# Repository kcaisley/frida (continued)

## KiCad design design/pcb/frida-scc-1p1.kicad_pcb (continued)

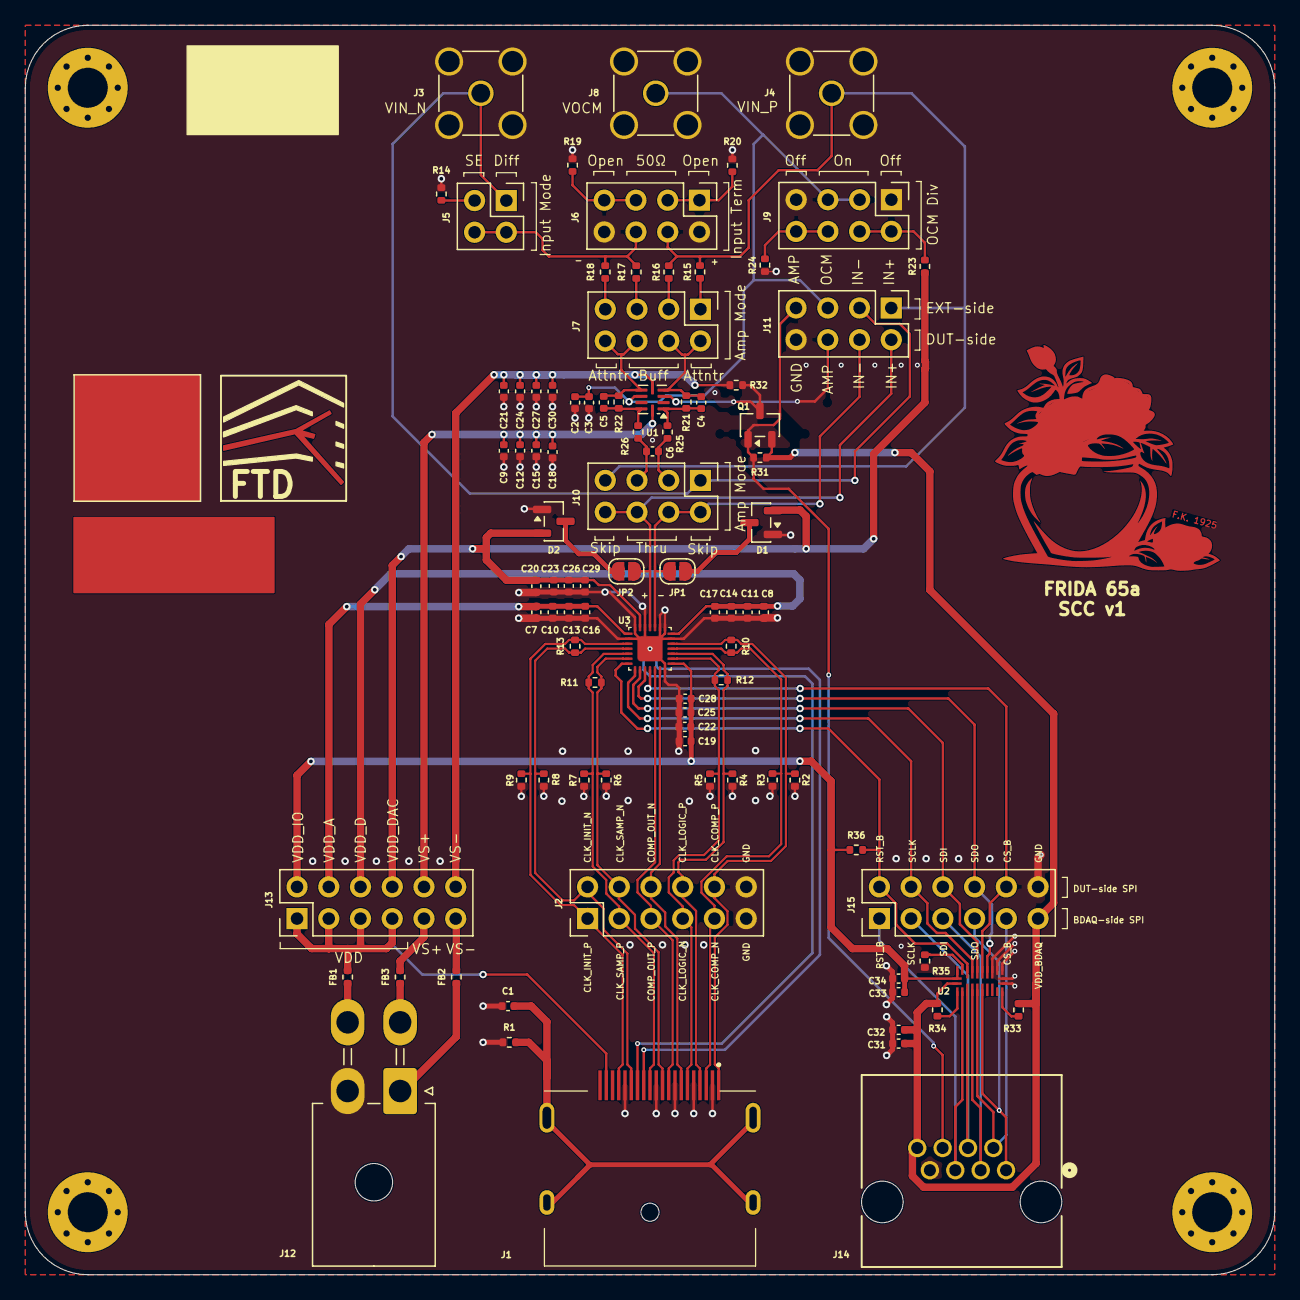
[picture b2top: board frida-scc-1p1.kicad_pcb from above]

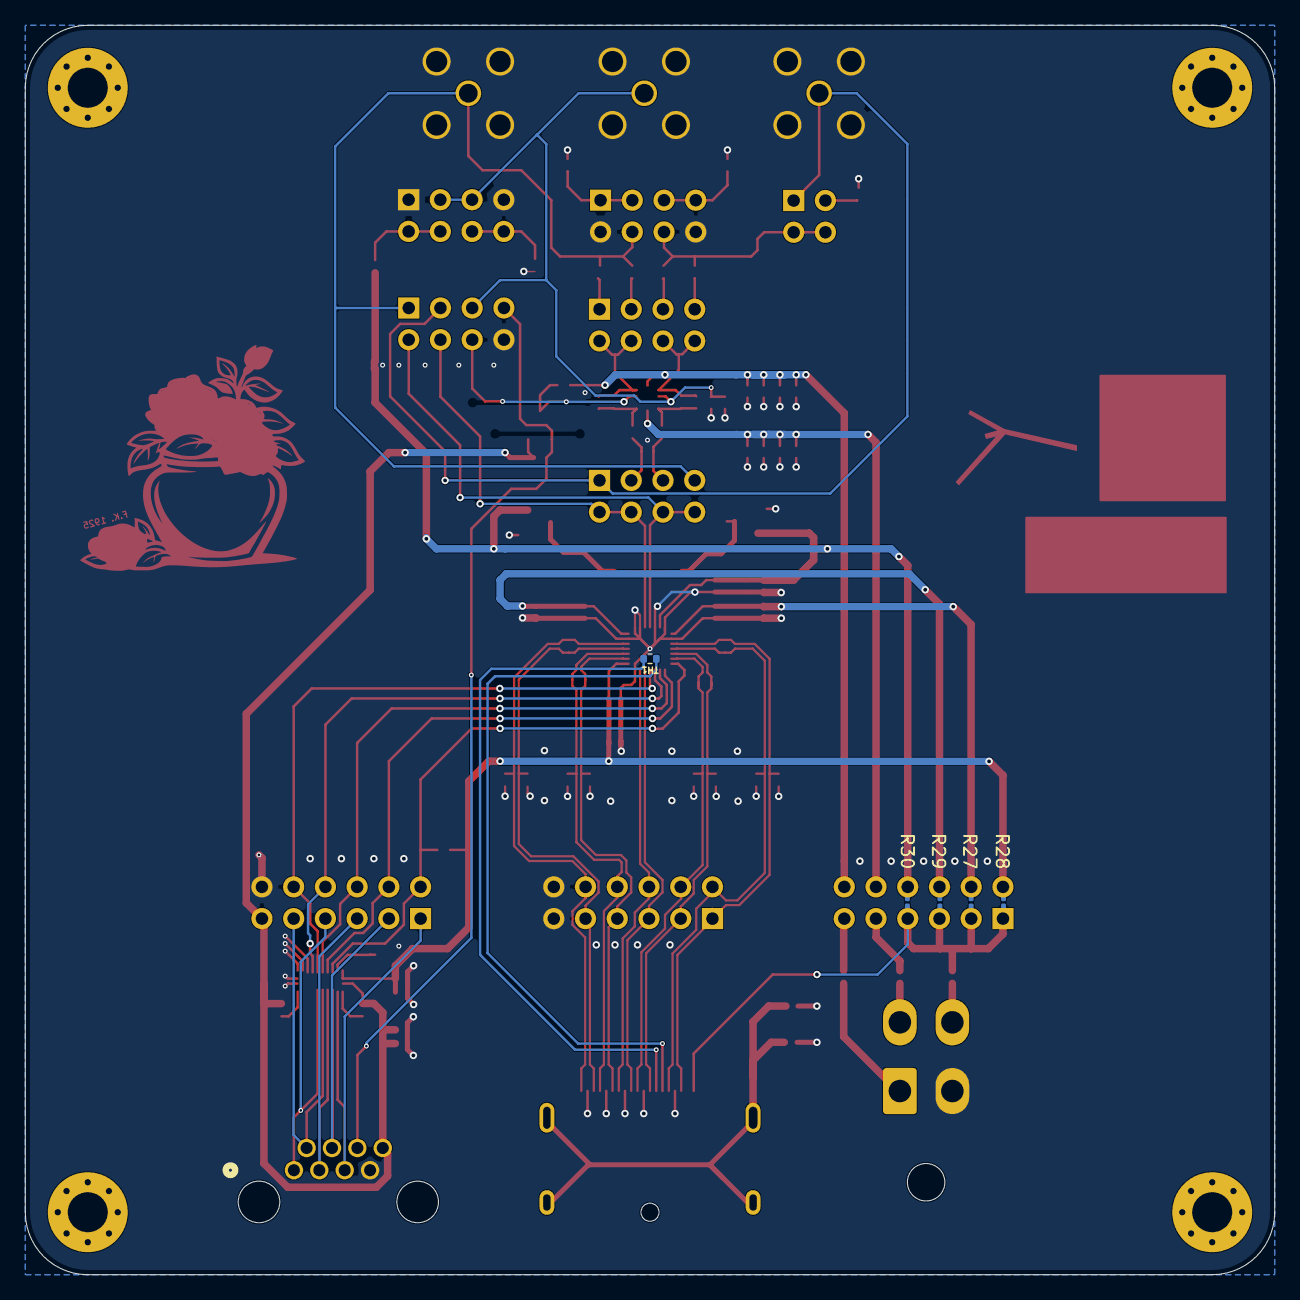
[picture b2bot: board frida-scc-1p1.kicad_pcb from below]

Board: 4 copper layers, 100.0 x 100.0 mm, 101 parts (5 on the bottom side), 65 nets.

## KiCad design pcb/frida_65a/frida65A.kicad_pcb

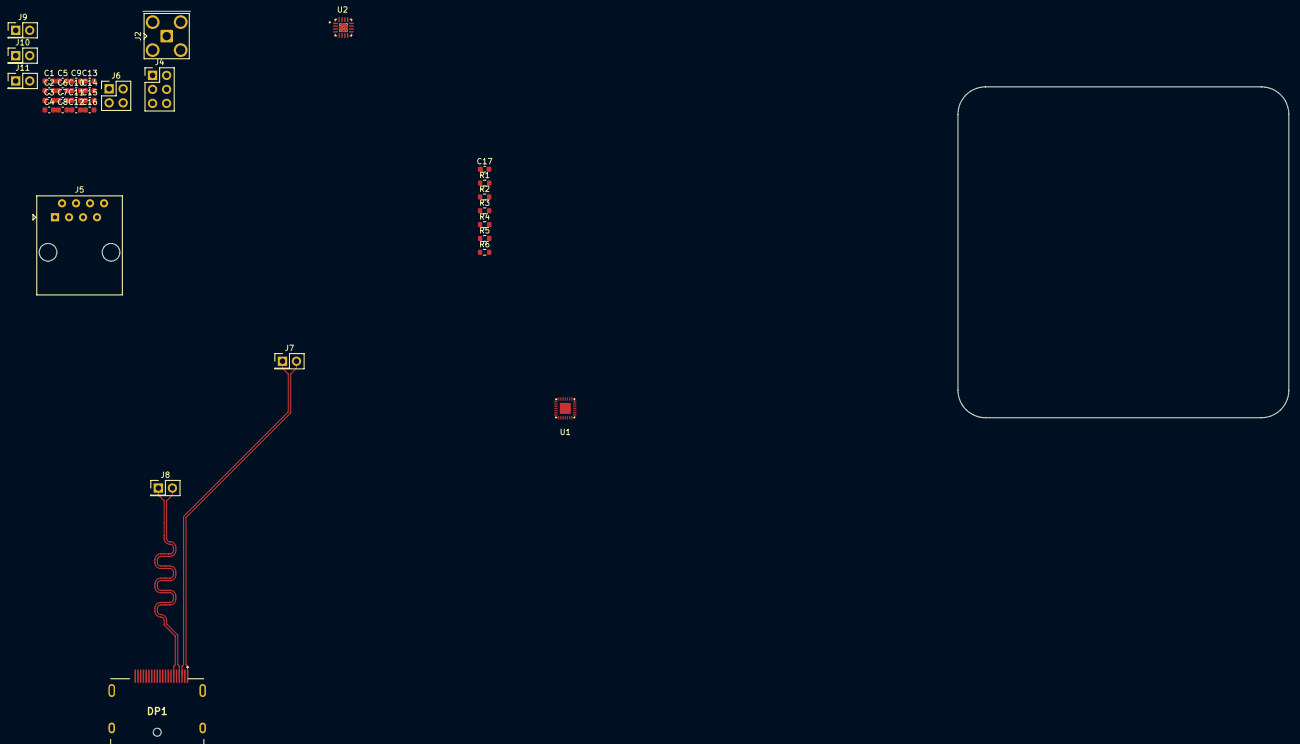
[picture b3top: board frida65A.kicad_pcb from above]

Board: 2 copper layers, 35 parts (0 on the bottom side), 23 nets.

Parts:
C1, C5, C9, C13: 47u; C_0603_1608Metric
C2, C6, C10, C14: 1u; C_0603_1608Metric
C3, C4, C7, C8, C11, C12, C15, C16, C17: 100n; C_0603_1608Metric
DP1: DP; DP_Molex_47272-0024
J2: CONN_IN_P; SMA_Amphenol_901-143_Horizontal
J4: TP_CFG; PinHeader_2x03_P2.54mm_Vertical
J5: CONN_CFG; RJ45_Amphenol_54602-x08_Horizontal
J6: TP_IN; PinHeader_2x02_P2.54mm_Vertical
J7: TP_INIT; PinHeader_2x01_P2.54mm_Vertical
J8: TP_SAMP; PinHeader_2x01_P2.54mm_Vertical
J9: TP_COMP; PinHeader_2x01_P2.54mm_Vertical
J10: TP_LOGIC; PinHeader_2x01_P2.54mm_Vertical
J11: TP_OUT; PinHeader_2x01_P2.54mm_Vertical
R1, R2, R3, R4, R5: 100; R_0603_1608Metric
R6: 10k; R_0603_1608Metric
U1: DUT; frida
U2: THS4520RGTT; QFN50P300X300X100-17N

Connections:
/CLK_COMP_N: DP1.7, J9.2, R3.1, U1.18 (CLK_COMP_N)
/CLK_COMP_P: DP1.9, J9.1, R3.2, U1.19 (CLK_COMP_P)
/CLK_INIT_N: DP1.1, J7.2, R1.1, U1.4 (CLK_INIT_N)
/CLK_INIT_P: DP1.3, J7.1, R1.2, U1.3 (CLK_INIT_P)
/CLK_LOGIC_N: DP1.10, J10.2, R4.1, U1.16 (CLK_LOGIC_N)
/CLK_LOGIC_P: DP1.12, J10.1, R4.2, U1.17 (CLK_LOGIC_P)
/CLK_SAMP_N: DP1.4, J8.2, R2.1, U1.6 (CLK_SAMP_N)
/CLK_SAMP_P: DP1.6, J8.1, R2.2, U1.5 (CLK_SAMP_P)
/COMP_OUT_N: DP1.15, J11.2, R5.1, U1.13 (COUP_OUT_N)
/COMP_OUT_P: DP1.17, J11.1, R5.2, U1.12 (COMP_OUT_P)
/RST_B: J4.5, J5.5, U1.7 (RST_B)
/SPI_CS_B: J4.1, J5.1, U1.11 (SPI_CS_B)
/SPI_SCLK: J4.4, J5.4, U1.8 (SPI_SCLK)
/SPI_SDI: J4.3, J5.3, U1.9 (SPI_SDI)
/SPI_SDO: J4.2, J5.2, U1.10 (SPI_SDO)
/VDD_A: C1.1, C2.1, C3.1, C4.1, U1.1 (VDD_A)
/VDD_D: C5.1, C6.1, C7.1, C8.1, U1.21 (VDD_D)
/VDD_DAC: C9.1, C10.1, C11.1, C12.1, U1.27 (VDD_DAC)
/VDD_IO: C13.1, C14.1, C15.1, C16.1, U1.15 (VDD_IO)
Earth: C17.1, DP1.MH1, DP1.MH2, DP1.MH3, DP1.MH4, R6.1
GND: C1.2, C2.2, C3.2, C4.2, C5.2, C6.2, C7.2, C8.2, C9.2, C10.2, C11.2, C12.2, C13.2, C14.2, C15.2, C16.2, C17.2, DP1.2, DP1.5, DP1.8, DP1.11, DP1.16, J2.2 (Ext), J4.6, J6.3, J6.4, R6.2, U1.2 (VSS_A), U1.14 (VSS_IO), U1.20 (VSS_D), U1.22 (VSS_D), U1.23 (VSS_D), U1.26 (VSS_DAC), U1.28 (VSS_A)
unnamed: J2.1 (In), J6.1, U1.25 (VIN_P)
unnamed: J6.2, U1.24 (VIN_N)

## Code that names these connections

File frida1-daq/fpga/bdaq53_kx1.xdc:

# ------------------------------------------------------------
# FRIDA DAQ - Constraints for BDAQ53 + Mercury KX1 (xc7k160t-1)
# ------------------------------------------------------------
#
# Pin sources:
#   System/Ethernet: bdaq53/firmware/src/bdaq53_KX1.xdc
#   DP5 pins:        Enclustra Mercury Master Pinout (Connector B)
#   RJ45 D pins:     bdaq53/firmware/src/bdaq53_KX1.xdc
#
# Signals not used by FRIDA (removed from bdaq53 reference):
#   Aurora / MGT (CLK_MGT_REF, MGT_REFCLK, MGT_RX, DP1 MGT AUX)
#   CLK200 oscillator, I2C, LEMO, PMOD, TLU (RJ45_TRIGGER/RESET)
#   mDP_ML (mini DisplayPort), GPIO_RESET, GPIO_SENSE, NTC_MUX
#   USER_BUTTON, derived clocks (I2C_CLK, SPI_CLK)

# ===== Clocks =====
create_clock -period 10.000 -name CLK_SYS -add [get_ports FCLK_IN]
create_clock -period 8.000 -name CLK_RGMII_RX -add [get_ports rgmii_rxc]

set_clock_groups -asynchronous \
    -group {BUS_CLK_PLL} \
    -group {CLK125PLLTX CLK125PLLTX90} \
    -group CLK_RGMII_RX \
    -group {SEQ_CLK_PLL}  ;# seq_gen config regs are stable before sequencer starts

# ===== SiTCP timing =====
set_max_delay -datapath_only -from [get_clocks CLK125PLLTX] -to [get_ports {rgmii_txd[*]}] 4.000
set_max_delay -datapath_only -from [get_clocks CLK125PLLTX] -to [get_ports rgmii_tx_ctl] 4.000
set_max_delay -datapath_only -from [get_clocks CLK125PLLTX90] -to [get_ports rgmii_txc] 4.000
set_property ASYNC_REG true [get_cells sitcp/SiTCP/GMII/GMII_TXCNT/irMacPauseExe_0]
set_property ASYNC_REG true [get_cells sitcp/SiTCP/GMII/GMII_TXCNT/irMacPauseExe_1]

# ===== System clock (100 MHz) =====
set_property PACKAGE_PIN AA3 [get_ports FCLK_IN]
set_property IOSTANDARD LVCMOS15 [get_ports FCLK_IN]

# ===== Reset button =====
set_property PACKAGE_PIN C18 [get_ports RESET_BUTTON]
set_property IOSTANDARD LVCMOS25 [get_ports RESET_BUTTON]
set_property PULLUP true [get_ports RESET_BUTTON]

# ===== User button (SW_USER_B, active low) =====
set_property PACKAGE_PIN AF22 [get_ports USER_BUTTON]
set_property IOSTANDARD LVCMOS25 [get_ports USER_BUTTON]
set_property PULLUP true [get_ports USER_BUTTON]

# ===== LEDs =====
# LED 0..3: onboard KX1 module LEDs (Bank 15, LVCMOS25)
set_property PACKAGE_PIN M17 [get_ports {LED[0]}]
set_property PACKAGE_PIN L18 [get_ports {LED[1]}]
set_property PACKAGE_PIN L17 [get_ports {LED[2]}]
set_property PACKAGE_PIN K18 [get_ports {LED[3]}]
# LED 4..7: BDAQ53 base board LEDs (LVCMOS25)
set_property PACKAGE_PIN P26 [get_ports {LED[4]}]
set_property PACKAGE_PIN M25 [get_ports {LED[5]}]
set_property PACKAGE_PIN L25 [get_ports {LED[6]}]
set_property PACKAGE_PIN P23 [get_ports {LED[7]}]
set_property IOSTANDARD LVCMOS25 [get_ports {LED[*]}]
set_property SLEW SLOW [get_ports LED*]

# ===== EEPROM (SPI for SiTCP) =====
set_property PACKAGE_PIN G14 [get_ports EEPROM_CS]
set_property PACKAGE_PIN H11 [get_ports EEPROM_SK]
set_property PACKAGE_PIN D8 [get_ports EEPROM_DI]
set_property PACKAGE_PIN A8 [get_ports EEPROM_DO]
set_property IOSTANDARD LVCMOS33 [get_ports EEPROM_*]

# ===== Ethernet (RGMII) =====
set_property SLEW FAST [get_ports mdio_phy_mdc]
set_property IOSTANDARD LVCMOS25 [get_ports mdio_phy_mdc]
set_property PACKAGE_PIN N16 [get_ports mdio_phy_mdc]

set_property SLEW FAST [get_ports mdio_phy_mdio]
set_property IOSTANDARD LVCMOS25 [get_ports mdio_phy_mdio]
set_property PACKAGE_PIN U16 [get_ports mdio_phy_mdio]

set_property SLEW FAST [get_ports phy_rst_n]
set_property IOSTANDARD LVCMOS25 [get_ports phy_rst_n]
set_property PACKAGE_PIN M20 [get_ports phy_rst_n]

set_property IOSTANDARD LVCMOS25 [get_ports rgmii_rxc]
set_property PACKAGE_PIN R21 [get_ports rgmii_rxc]
set_property IOSTANDARD LVCMOS25 [get_ports rgmii_rx_ctl]
set_property PACKAGE_PIN P21 [get_ports rgmii_rx_ctl]
set_property IOSTANDARD LVCMOS25 [get_ports {rgmii_rxd[0]}]
set_property PACKAGE_PIN P16 [get_ports {rgmii_rxd[0]}]
set_property IOSTANDARD LVCMOS25 [get_ports {rgmii_rxd[1]}]
set_property PACKAGE_PIN N17 [get_ports {rgmii_rxd[1]}]
set_property IOSTANDARD LVCMOS25 [get_ports {rgmii_rxd[2]}]
set_property PACKAGE_PIN R16 [get_ports {rgmii_rxd[2]}]
set_property IOSTANDARD LVCMOS25 [get_ports {rgmii_rxd[3]}]
set_property PACKAGE_PIN R17 [get_ports {rgmii_rxd[3]}]

set_property SLEW FAST [get_ports rgmii_txc]
set_property IOSTANDARD LVCMOS25 [get_ports rgmii_txc]
set_property PACKAGE_PIN R18 [get_ports rgmii_txc]
set_property SLEW FAST [get_ports rgmii_tx_ctl]
set_property IOSTANDARD LVCMOS25 [get_ports rgmii_tx_ctl]
set_property PACKAGE_PIN P18 [get_ports rgmii_tx_ctl]
set_property SLEW FAST [get_ports {rgmii_txd[0]}]
set_property IOSTANDARD LVCMOS25 [get_ports {rgmii_txd[0]}]
set_property PACKAGE_PIN N18 [get_ports {rgmii_txd[0]}]
set_property SLEW FAST [get_ports {rgmii_txd[1]}]
set_property IOSTANDARD LVCMOS25 [get_ports {rgmii_txd[1]}]
set_property PACKAGE_PIN M19 [get_ports {rgmii_txd[1]}]
set_property SLEW FAST [get_ports {rgmii_txd[2]}]
set_property IOSTANDARD LVCMOS25 [get_ports {rgmii_txd[2]}]
set_property PACKAGE_PIN U17 [get_ports {rgmii_txd[2]}]
set_property SLEW FAST [get_ports {rgmii_txd[3]}]
set_property IOSTANDARD LVCMOS25 [get_ports {rgmii_txd[3]}]
set_property PACKAGE_PIN T17 [get_ports {rgmii_txd[3]}]

# ===== FRIDA chip: DP5 (DP_ML, SelectIOs) =====
# 4 LVDS pairs (sequencer clocks) + AUX (comp_out)
# Pin mapping from Enclustra Mercury Master Pinout, Connector B
set_property PACKAGE_PIN K16 [get_ports CLK_INIT_P]
set_property PACKAGE_PIN K17 [get_ports CLK_INIT_N]
set_property PACKAGE_PIN L19 [get_ports CLK_SAMP_P]
set_property PACKAGE_PIN L20 [get_ports CLK_SAMP_N]
set_property PACKAGE_PIN H17 [get_ports CLK_COMP_P]
set_property PACKAGE_PIN H18 [get_ports CLK_COMP_N]
set_property PACKAGE_PIN G19 [get_ports CLK_LOGIC_P]
set_property PACKAGE_PIN F20 [get_ports CLK_LOGIC_N]
set_property IOSTANDARD LVDS_25 [get_ports CLK_*_P]
set_property IOSTANDARD LVDS_25 [get_ports CLK_*_N]
set_property PACKAGE_PIN H19 [get_ports COMP_OUT_P]
set_property PACKAGE_PIN G20 [get_ports COMP_OUT_N]
set_property IOSTANDARD LVDS_25 [get_ports COMP_OUT_*]

# ===== FRIDA chip: RJ45 port D (single-ended) =====
# 4 diff pairs = 8 pins, used as single-ended for SPI + GPIO
# Pin mapping from bdaq53_KX1.xdc (RJ45 D / IOD block)
# Signal-to-pin assignment from SCC schematic (J12 RJ45 pinout):
#   Pin 1: SPI_CS_B  → A18  (DATA_B4_P)
#   Pin 2: SPI_SDO   → A19  (DATA_B4_N)
#   Pin 3: SPI_SDI   → F17  (DATA_B2_N)
#   Pin 4: SPI_SCLK  → E15  (DATA_B3_P)
#   Pin 5: RST_B     → E16  (DATA_B3_N)
#   Pin 6: AMPEN_B   → E17  (DATA_B2_P)
#   Pin 7: VSS_LS → G15  (DATA_B1_P, level shifter VCCB low ref)
#   Pin 8: VDD_LS → F15  (DATA_B1_N, level shifter VCCB high ref)
set_property PACKAGE_PIN G15 [get_ports VSS_LS]
set_property PACKAGE_PIN F15 [get_ports VDD_LS]
set_property IOSTANDARD LVCMOS25 [get_ports V*_LS]
set_property PACKAGE_PIN A18 [get_ports SPI_CS_B]
set_property PACKAGE_PIN A19 [get_ports SPI_SDO]
set_property PACKAGE_PIN F17 [get_ports SPI_SDI]
set_property PACKAGE_PIN E15 [get_ports SPI_SCLK]
set_property PACKAGE_PIN E16 [get_ports RST_B]
set_property PACKAGE_PIN E17 [get_ports AMPEN_B]
set_property IOSTANDARD LVCMOS25 [get_ports SPI_*]
set_property IOSTANDARD LVCMOS25 [get_ports RST_B]
set_property IOSTANDARD LVCMOS25 [get_ports AMPEN_B]

# ===== SPI configuration flash =====
set_property CONFIG_MODE SPIx4 [current_design]
set_property BITSTREAM.GENERAL.COMPRESS TRUE [current_design]
set_property BITSTREAM.CONFIG.CONFIGRATE 33 [current_design]
